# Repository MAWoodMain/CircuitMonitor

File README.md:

# CircuitMonitor
A fully integrated system to monitor power consumption on a circuit by circuit basis.

## The Plan
The system will consist of two board, a mains board and a analog front end (AFE).

The mains board shall perform two roles, it will generate a 5V supply to power the second board and the RPI it sits on and it will step down and isolate the mains voltage for voltage sensing.

The AFE will measure 12 current channels and one voltage channel. The current channels will be monitored with either Rogowski coils or current sense transformers, this will ensure galvanic isolation.

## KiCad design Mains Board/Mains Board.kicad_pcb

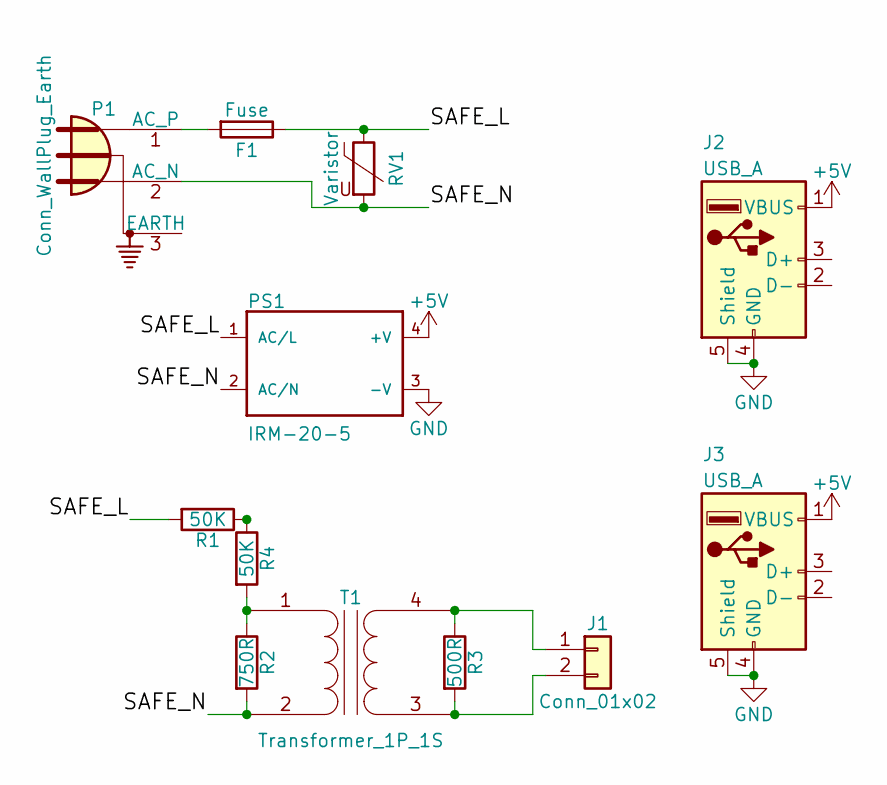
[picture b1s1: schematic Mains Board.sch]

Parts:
F1: Fuse; Fuseholder5x20_horiz_SemiClosed_Casing10x25mm
J1: Conn_01x02; Pin_Header_Straight_1x02_Pitch2.54mm
J2, J3: USB_A; USB_A_Vertical
P1: Conn_WallPlug_Earth; PX0580
PS1: IRM-20-5
R1, R4: 50K; R_2512
R2: 750R; R_2512
R3: 500R; R_2512
RV1: Varistor; ERZ-V20D511
T1: Transformer_1P_1S; PA3000NL

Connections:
+5V: J2.1 (VBUS), J3.1 (VBUS), PS1.4 (+V)
/SAFE_L: F1.1, PS1.1 (AC/L), R1.2, RV1.1
/SAFE_N: P1.2 (AC_N), PS1.2 (AC/N), R2.2, RV1.2, T1.2 (AB)
GND: J2.4 (GND), J2.5 (Shield), J3.4 (GND), J3.5 (Shield), PS1.3 (-V)
unnamed: F1.2, P1.1 (AC_P)
unnamed: J1.1, R3.1, T1.4 (SB)
unnamed: J1.2, R3.2, T1.3 (SA)
unnamed: R1.1, R4.1
unnamed: R2.1, R4.2, T1.1 (AA)

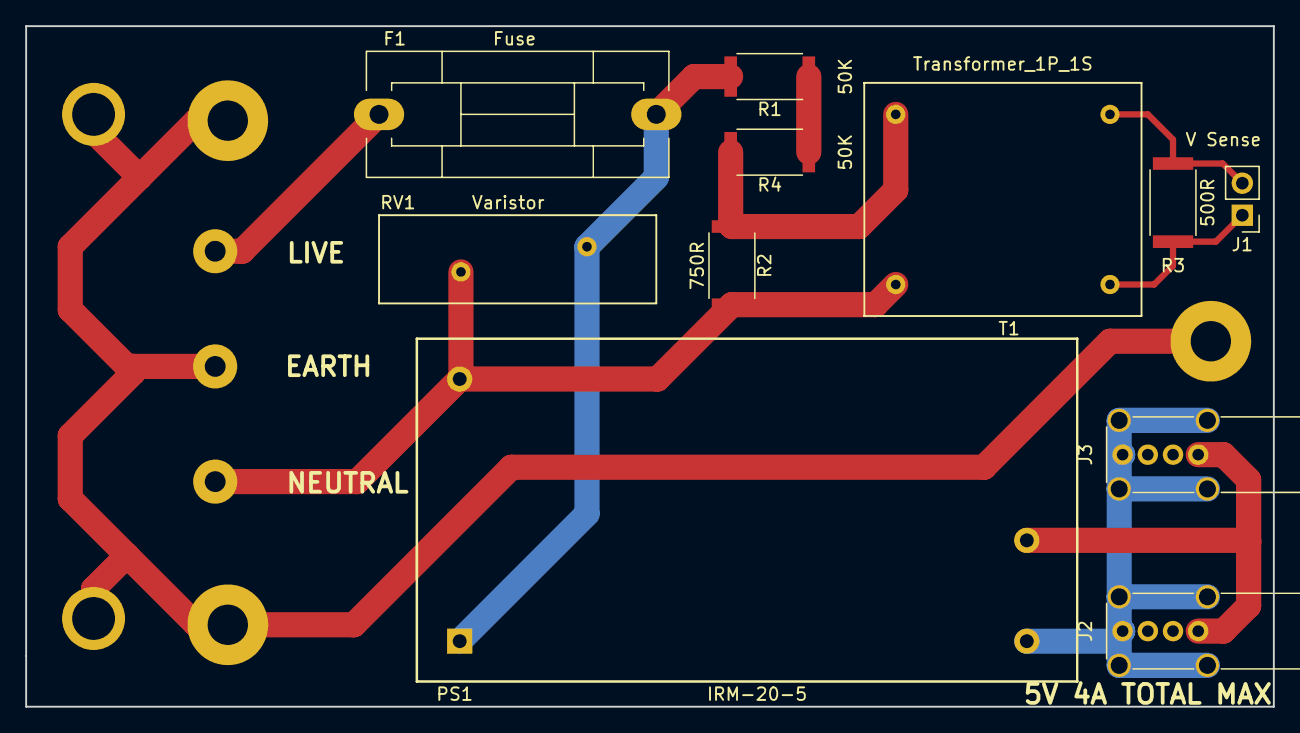
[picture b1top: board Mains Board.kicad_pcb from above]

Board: 2 copper layers, 99.0 x 54.0 mm, 12 parts (0 on the bottom side), 9 nets.

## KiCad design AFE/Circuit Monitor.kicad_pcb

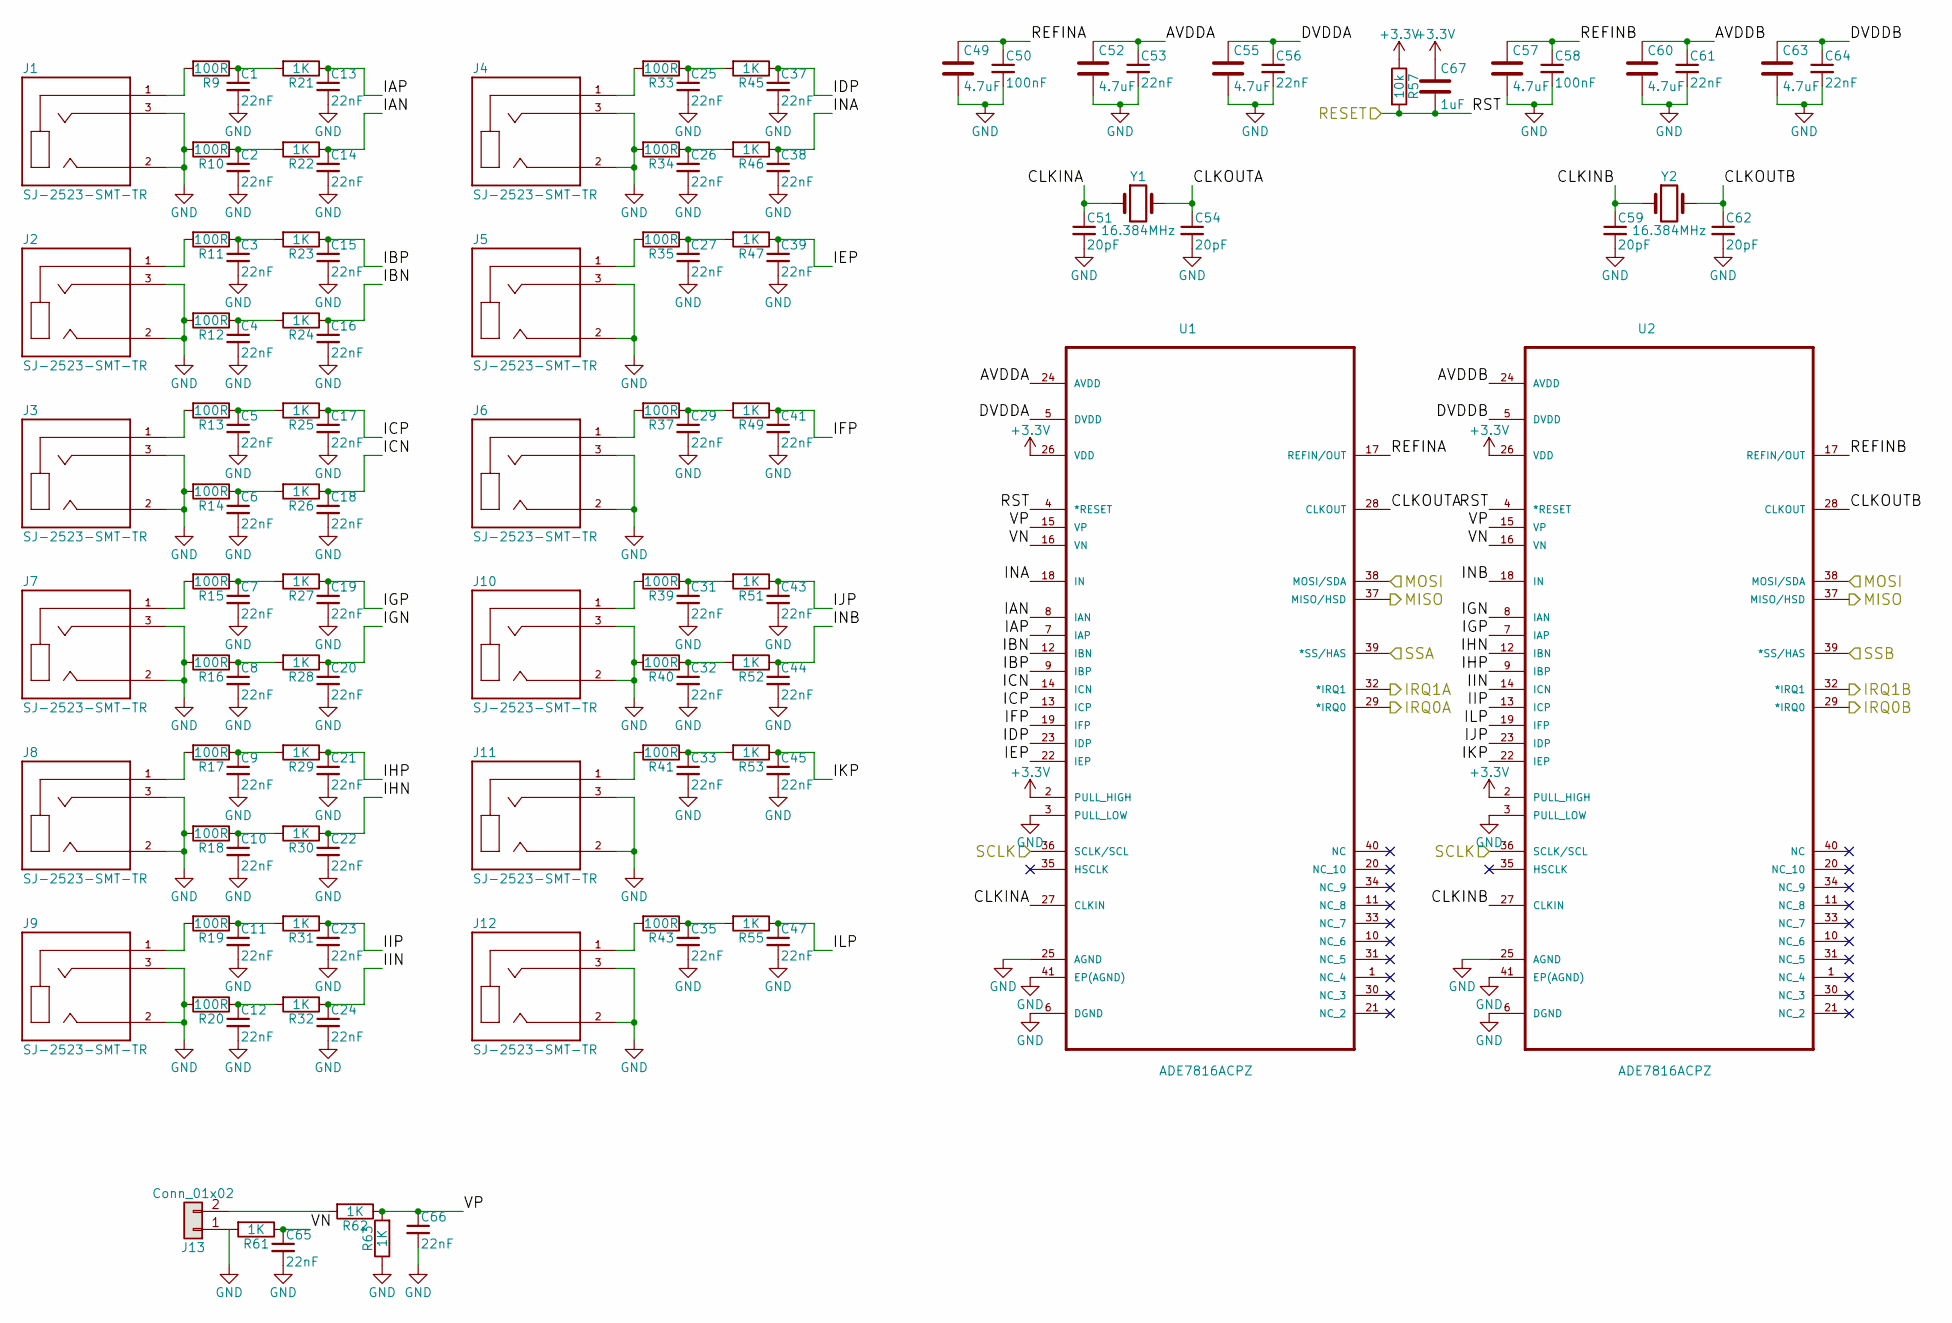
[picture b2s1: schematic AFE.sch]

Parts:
C1, C2, C3, C4, C5, C6, C7, C8, C9, C10, C11, C12, C13, C14, C15, C16, C17, C18, C19, C20, C21, C22, C23, C24, C25, C26, C27, C29, C31, C32, C33, C35, C37, C38, C39, C41, C43, C44, C45, C47, C53, C56, C61, C64, C65, C66: 22nF; C_0603_HandSoldering
C49, C52, C55, C57, C60, C63: 4.7uF; CP_Elec_4x5.3
C50, C58: 100nF; C_0603_HandSoldering
C51, C54, C59, C62: 20pF; C_0603_HandSoldering
C67: 1uF; C_0603_HandSoldering
J1, J2, J3, J4, J5, J6, J7, J8, J9, J10, J11, J12: SJ-2523-SMT-TR; CUI_SJ-2523-SMT-TR
J13: Conn_01x02; Pin_Header_Angled_1x02_Pitch2.54mm
R9, R10, R11, R12, R13, R14, R15, R16, R17, R18, R19, R20, R33, R34, R35, R37, R39, R40, R41, R43: 100R; R_0603_HandSoldering
R21, R22, R23, R24, R25, R26, R27, R28, R29, R30, R31, R32, R45, R46, R47, R49, R51, R52, R53, R55, R61, R62, R63: 1K; R_0603_HandSoldering
R57: 10k; R_0603_HandSoldering
U1, U2: ADE7816ACPZ; QFN50P600X600X80-41N
Y1, Y2: 16.384MHz; Crystal_SMD_HC49-SD

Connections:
+3V3: C67.1, R57.1, U1.2 (PULL_HIGH), U1.26 (VDD), U2.2 (PULL_HIGH), U2.26 (VDD); also elsewhere on the board
/AFE/AVDDA: C52.1, C53.1, U1.24 (AVDD)
/AFE/AVDDB: C60.1, C61.1, U2.24 (AVDD)
/AFE/CLKINA: C51.1, U1.27 (CLKIN), Y1.1
/AFE/CLKINB: C59.1, U2.27 (CLKIN), Y2.1
/AFE/CLKOUTA: C54.1, U1.28 (CLKOUT), Y1.2
/AFE/CLKOUTB: C62.1, U2.28 (CLKOUT), Y2.2
/AFE/DVDDA: C55.1, C56.1, U1.5 (DVDD)
/AFE/DVDDB: C63.1, C64.1, U2.5 (DVDD)
/AFE/IAN: C14.1, R22.1, U1.8 (IAN)
/AFE/IAP: C13.1, R21.1, U1.7 (IAP)
/AFE/IBN: C16.1, R24.1, U1.12 (IBN)
/AFE/IBP: C15.1, R23.1, U1.9 (IBP)
/AFE/ICN: C18.1, R26.1, U1.14 (ICN)
/AFE/ICP: C17.1, R25.1, U1.13 (ICP)
/AFE/IDP: C37.1, R45.1, U1.23 (IDP)
/AFE/IEP: C39.1, R47.1, U1.22 (IEP)
/AFE/IFP: C41.1, R49.1, U1.19 (IFP)
/AFE/IGN: C20.1, R28.1, U2.8 (IAN)
/AFE/IGP: C19.1, R27.1, U2.7 (IAP)
/AFE/IHN: C22.1, R30.1, U2.12 (IBN)
/AFE/IHP: C21.1, R29.1, U2.9 (IBP)
/AFE/IIN: C24.1, R32.1, U2.14 (ICN)
/AFE/IIP: C23.1, R31.1, U2.13 (ICP)
/AFE/IJP: C43.1, R51.1, U2.23 (IDP)
/AFE/IKP: C45.1, R53.1, U2.22 (IEP)
/AFE/ILP: C47.1, R55.1, U2.19 (IFP)
/AFE/INA: C38.1, R46.1, U1.18 (IN)
/AFE/INB: C44.1, R52.1, U2.18 (IN)
/AFE/REFINA: C49.1, C50.1, U1.17 (REFIN/OUT)
/AFE/REFINB: C57.1, C58.1, U2.17 (REFIN/OUT)
/AFE/VN: C65.1, R61.1, U1.16 (VN), U2.16 (VN)
/AFE/VP: C66.1, R62.1, R63.2, U1.15 (VP), U2.15 (VP)
/IRQ0A: U1.29 (*IRQ0); also elsewhere on the board
/IRQ0B: U2.29 (*IRQ0); also elsewhere on the board
/IRQ1A: U1.32 (*IRQ1); also elsewhere on the board
/IRQ1B: U2.32 (*IRQ1); also elsewhere on the board
/MISO: U1.37 (MISO/HSD), U2.37 (MISO/HSD); also elsewhere on the board
/MOSI: U1.38 (MOSI/SDA), U2.38 (MOSI/SDA); also elsewhere on the board
/RST: C67.2, R57.2, U1.4 (*RESET), U2.4 (*RESET); also elsewhere on the board
/SCLK: U1.36 (SCLK/SCL), U2.36 (SCLK/SCL); also elsewhere on the board
/SSA: U1.39 (*SS/HAS); also elsewhere on the board
/SSB: U2.39 (*SS/HAS); also elsewhere on the board
GND: C1.2, C2.2, C3.2, C4.2, C5.2, C6.2, C7.2, C8.2, C9.2, C10.2, C11.2, C12.2, C13.2, C14.2, C15.2, C16.2, C17.2, C18.2, C19.2, C20.2, C21.2, C22.2, C23.2, C24.2, C25.2, C26.2, C27.2, C29.2, C31.2, C32.2, C33.2, C35.2, C37.2, C38.2, C39.2, C41.2, C43.2, C44.2, C45.2, C47.2, C49.2, C50.2, C51.2, C52.2, C53.2, C54.2, C55.2, C56.2, C57.2, C58.2, C59.2, C60.2, C61.2, C62.2, C63.2, C64.2, C65.2, C66.2, J1.2, J1.3, J2.2, J2.3, J3.2, J3.3, J4.2, J4.3, J5.2, J5.3, J6.2, J6.3, J7.2, J7.3, J8.2, J8.3, J9.2, J9.3, J10.2, J10.3, J11.2, J11.3, J12.2, J12.3, J13.1, R10.2, R12.2, R14.2, R16.2, R18.2, R20.2, R34.2, R40.2, R61.2, R63.1, U1.3 (PULL_LOW), U1.6 (DGND), U1.25 (AGND), U1.41 (EP(AGND)), U2.3 (PULL_LOW), U2.6 (DGND), U2.25 (AGND), U2.41 (EP(AGND)); also elsewhere on the board
unnamed: C1.1, R9.1, R21.2
unnamed: C2.1, R10.1, R22.2
unnamed: C3.1, R11.1, R23.2
unnamed: C4.1, R12.1, R24.2
unnamed: C5.1, R13.1, R25.2
unnamed: C6.1, R14.1, R26.2
unnamed: C7.1, R15.1, R27.2
unnamed: C8.1, R16.1, R28.2
unnamed: C9.1, R17.1, R29.2
unnamed: C10.1, R18.1, R30.2
unnamed: C11.1, R19.1, R31.2
unnamed: C12.1, R20.1, R32.2
unnamed: C25.1, R33.1, R45.2
unnamed: C26.1, R34.1, R46.2
unnamed: C27.1, R35.1, R47.2
unnamed: C29.1, R37.1, R49.2
unnamed: C31.1, R39.1, R51.2
unnamed: C32.1, R40.1, R52.2
unnamed: C33.1, R41.1, R53.2
unnamed: C35.1, R43.1, R55.2
unnamed: J1.1, R9.2
unnamed: J2.1, R11.2
unnamed: J3.1, R13.2
unnamed: J4.1, R33.2
unnamed: J5.1, R35.2
unnamed: J6.1, R37.2
unnamed: J7.1, R15.2
unnamed: J8.1, R17.2
unnamed: J9.1, R19.2
unnamed: J10.1, R39.2
unnamed: J11.1, R41.2
unnamed: J12.1, R43.2
unnamed: J13.2, R62.2

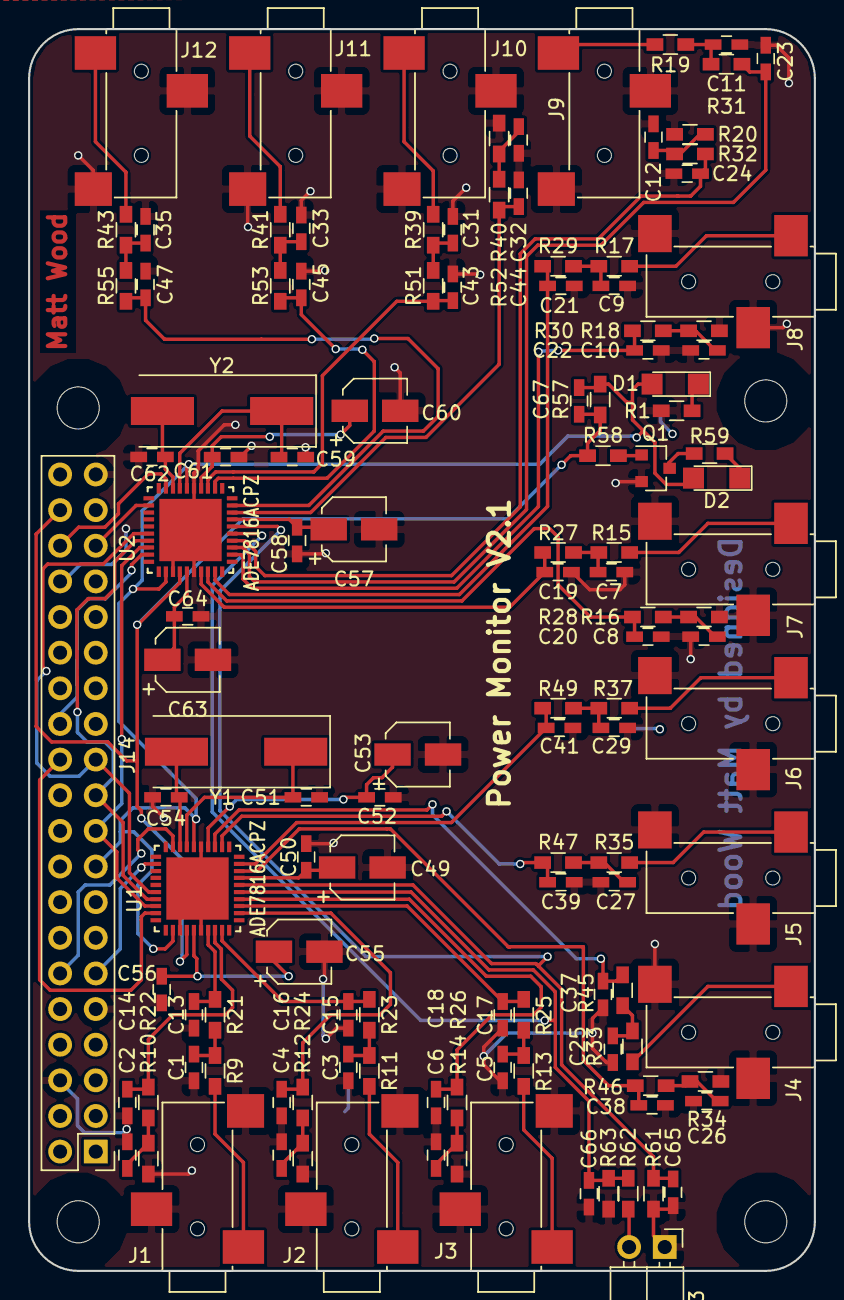
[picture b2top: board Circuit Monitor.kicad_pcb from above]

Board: 2 copper layers, 56.0 x 88.5 mm, 127 parts (0 on the bottom side), 81 nets.

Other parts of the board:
D1: 862-4566; LED_1206
D2: 862-4572; LED_1206
J14: Raspberry_Pi_2_3; Pin_Header_Straight_2x20_Pitch2.54mm
Q1: MMBT3904; SOT-23
R1, R59: 68R; R_0603_HandSoldering
R58: 1K; R_0603_HandSoldering

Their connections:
+3V3: D1.2, D2.2, J14.1, J14.17; also elsewhere on the board
/IRQ0A: J14.12; also elsewhere on the board
/IRQ0B: J14.36; also elsewhere on the board
/IRQ1A: J14.11; also elsewhere on the board
/IRQ1B: J14.35; also elsewhere on the board
/MISO: J14.21; also elsewhere on the board
/MOSI: J14.19; also elsewhere on the board
/RST: J14.38, R58.1; also elsewhere on the board
/SCLK: J14.23; also elsewhere on the board
/SSA: J14.24; also elsewhere on the board
/SSB: J14.26; also elsewhere on the board
GND: J14.6, J14.9, J14.14, J14.20, J14.25, J14.30, J14.34, J14.39, Q1.2, R1.2; also elsewhere on the board
unnamed: D1.1, R1.1
unnamed: D2.1, R59.1
unnamed: Q1.1, R58.2
unnamed: Q1.3, R59.2

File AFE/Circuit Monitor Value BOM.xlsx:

Qty | Reference(s) | Value
54 | C1,2,3,4,5,6,7,8,9,10,11,12,13,14,15,16 | 22nF
 | C17,18,19,20,21,22,23,24,25,26,27,28,29 | 22nF
 | C30,31,32,33,34,35,36,37,38,39,40,41,42 | 22nF
 | C43,44,45,46,47,48,53,56,61,64,65,66 | 22nF
6 | C49,52,55,57,60,63 | 4.7uF
2 | C50,58 | 100nF
4 | C51,54,59,62 | 20pF
1 | D1 | 862-4566
1 | D2 | 862-4572
12 | J1,2,3,4,5,6,7,8,9,10,11,12 | SJ-2523-SMT-TR
1 | Q1 | MMBT3904
2 | R1,59 | 68R
24 | R9,10,11,12,13,14,15,16,17,18,19,20,33 | 100R
 | R34,35,36,37,38,39,40,41,42,43,44 | 100R
27 | R21,22,23,24,25,26,27,28,29,30,31,32,45 | 1K
 | R46,47,48,49,50,51,52,53,54,55,56,58,61,62 | 1K
1 | R57 | 10k
1 | R63 | ?
2 | U1,2 | ADE7816ACPZ
2 | Y1,2 | 16.384MHz

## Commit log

2018-08-12 Added EDA files to GIT
2018-08-12 Added measurement card diagram
2018-08-12 Fixed diagram error
2018-08-12 Added back plane diagram
2018-08-12 Fixed diagram mistake
2018-08-12 More schematic progress and removed diagrams to fix bug
2018-08-12 Readdded diagrams
2018-08-12 Switched to jpeg
2018-08-12 Switched back to png
2018-09-16 Finished mains board design and AFE design, design no longer uses measurement cards, rather a single RPI HAT that support 12 channels for current
2018-09-16 Updated readme to match current plan
2018-09-16 Removed old diagrams
